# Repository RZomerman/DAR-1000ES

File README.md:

# Sony DAR-1000ES Conversion Project

This repository contains the project documentation converted from the original Word document into chapter-based GitHub Flavored Markdown.

## Chapters

For current AHCT wiring, brightness calculations and radio operation, start
with the [screen-driver operating guide](13-screen-driver-operating-guide.md).
Shared STB on **both** TD chips corrected the earlier multiplexing corruption;
clean 22-matrix text and scrolling were observed. Firmware 0.3.28 includes
internet radio, explicitly authorized full-width NOW PLAYING, and source
channel/bitrate/playback/genre indicators.
Installed 0.3.29 adds selectable Option 1 stereo spectrum (11 real PCM frequency
bands per channel), verified with isolated TD-model captures and decoded
stereo/mono/silence fixtures; the user confirmed the bars at 0.75% brightness.
Version 0.3.30 adds MONO 1/2 bank labels while retaining actual-source STEREO
and fixes measured scan gaps with longer DMA batching. A connected camera
snapshot confirms all 22 bars and STEREO/MONO 1/MONO 2/TUNED at 0.75%
per-grid duty. User confirmation of residual flicker is still pending;
a still image cannot establish temporal stability.
Physical voltage/current validation remains outstanding.
Firmware 0.3.31 boots with the fixed AHCT v2 GPIO map. Display output still
starts stopped; the legacy profile remains an isolated-only runtime option.
Installed firmware 0.3.32 adds eight display modes and shared short-/long-press
controls for a future Display Mode button, with 0.25% / 0.5% / 0.75% DIM cycling.
All eight modes and DIM cycling were checked on the isolated ESP; after
reconnection, Equalizer was restored at 0.75% per-grid duty.

For current display control, start with the
[fixed-element guide](08-esp-display-driver-specification.md#6-fixed-element-control-guide)
and [generic 5x7 matrix guide](08-esp-display-driver-specification.md#7-generic-5x7-matrix-guide).
The [annotated reference comparison](media/display-reference-coverage.svg)
matches every functional symbol in the FL701 drawing to an observed command.
Element mapping is complete at that level. Clean full-screen multiplexing
has now been observed with shared STB; electrical validation remains outstanding.

The [complete display bitmap catalogue](10-display-bitmap-catalogue.md)
includes 5x7 pixel patterns and HEX values for uppercase/lowercase letters,
digits, punctuation, a music note and seven level bars.

1. [DAR-1000ES Conversion](01-conversion.md)
2. [DAR-1000ES Display Control](02-display-control.md)
3. [DAR-1000ES Sound Path](03-sound-path.md)
4. [DAR-1000ES Program and Keypad Baseline](04-program-and-keypad-baseline.md)
5. [Bus Capture Findings and Key Reports](05-bus-capture-findings.md)
6. [Direct Display driving](06-direct-display-driving.md)
7. [Audio Control Findings and Next-Step Plan](07-audio-control-findings-and-plan.md)
8. [ESP32 Display-Driver Specification](08-esp-display-driver-specification.md)
9. [Music Note Bitmap](09-music-note-bitmap.md)
10. [Display Bitmap Catalogue](10-display-bitmap-catalogue.md)
11. [Live ESP32 Display Driver and Validation](11-live-display-driver-and-validation.md)
12. [TD62C950RF Timing Revalidation](12-td62c950rf-timing-revalidation.md)
13. [Screen Driver Operating Guide](13-screen-driver-operating-guide.md)

Images used by the chapters are stored in [`media/`](media/).

The [ESP32 firmware](firmware/README-DAR-1000ES.md) includes internet radio,
the opt-in display timing/NOW PLAYING profile and the preserved upstream license.

## Control Integration Options

1. **Reuse the original controls (partially characterized):** Investigate the parallel bus between the system controller and display/front-panel controller IC701 before bypassing the original control firmware. See the [internal bus protocol specification](SONY_DAR1000ES_Protocol_Spec.md) and [2026-11-02 capture findings](05-bus-capture-findings.md). Passive captures establish repeatable framing and key/display correlations, but masked bits, driver ownership and electrical assumptions still block reliable emulation.
2. **Direct display-driver control (optically mapped, driver experimental):** Captures at IC702/IC703 establish a 26-slot scan, 40 segment clocks and one grid clock per slot. Controlled one-hot tests now map all 770 matrix dots and all fixed functional elements shown in the reference. See the [operating guide](13-screen-driver-operating-guide.md), [element guide](08-esp-display-driver-specification.md) and [capture/validation history](06-direct-display-driving.md). Shared STB on both TD chips now gives clean full-width text and scrolling; electrical margins and current remain unverified. [DAR-1000ES Display Control](02-display-control.md) retains the original hardware proposal, not current wiring instructions.

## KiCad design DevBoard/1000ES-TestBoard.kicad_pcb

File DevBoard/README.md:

# Sony DAR-1000ES ESP32 Development Board

## Overview

**Design proposal, not a hardware-validation report.** This document describes
the intended three-ESP development board, not the pinout of the current
display-test harness. The [current display-control guide](../08-esp-display-driver-specification.md)
records confirmed element mapping; it does not establish that this board's
audio, bus, keypad, power or isolation features have been validated.

This development board is designed as the primary hardware platform for the **Sony DAR-1000ES modernization project**. It enables rapid experimentation with multiple integration strategies while preserving the original Sony hardware wherever possible.

The board incorporates **three ESP32-S3 controllers**, although only two are expected to be required for the final solution. The third controller is included specifically as a contingency path for direct display control if communication through the original Sony system controller (IC701) proves impractical.

The objective of this board is to validate all critical hardware interfaces before committing to a final production design.

---

## Design Goals

The board supports testing of four major functional areas:

### 1. Digital Audio Injection

A dedicated Audio ESP is responsible for generating digital audio and feeding it directly into the Sony audio processing chain.

Target interface:

| Signal | Destination |
|----------|----------|
| ATT/SHIFT/LATCH | IC501 |
| LRCKI | IC501 |
| DATAI | IC501 |
| BCKI | IC501 |

This allows the DAR-1000ES to receive modern digital audio streams while continuing to use the original Sony DAC and audio circuitry.

---

### 2. IC701 Controller Bus Injection

The primary Controller ESP is intended to test emulation and injection on the internal Sony communication bus. **This has not been validated.** This is **Option 1**: investigate retaining IC701, the display/front-panel controller, and the default controls before directly driving IC702 and IC703.

See the [unvalidated internal bus protocol proposal](../SONY_DAR1000ES_Protocol_Spec.md) for the working hypotheses and required validation. Signal directions, timing, electrical assumptions, and message formats are not established.

Supported signals:

| Signal |
|----------|
| DBS0-DBS7 |
| ACK |
| STB |
| REQ |
| NCK |

The intention is to determine whether the original firmware architecture can be leveraged by communicating with IC701 over its interface to the system controller.

If successful, this becomes the preferred approach because it preserves most of the original Sony subsystem interactions.

---

### 2b. Direct Sony Hardware Control

In addition to bus injection, the Controller ESP can directly control critical DAR-1000ES hardware signals.

Supported outputs include:

| Function |
|----------|
| D.MUTE |
| A.MUTE |
| Audio Relay |
| Power Control |
| Reset Control |

These are intended control outputs, not established safe drive procedures.
Verify their actual voltage, polarity, ownership and reset behavior before
using them, even if communication through the original controller fails.

---

### 2c. Keypad Matrix Interface

The board provides direct access to the original Sony button matrix.

Capabilities:

- Scan front-panel buttons
- Decode keypad presses
- Replace original controller functionality
- Support future custom user interface options

The proposed keypad interface uses a dedicated keypad controller. Isolate
IC701 from all fourteen matrix nets before enabling another scanner;
reliable operation and physical key positions still need validation.
See the [keypad design baseline](../04-program-and-keypad-baseline.md).

---

### 3. Direct Display Driver Control (Fallback Strategy)

A third ESP32-S3 is included exclusively as a backup solution.

If direct IC701 bus injection does not provide sufficient control of the front-panel display, this ESP can take over the display subsystem directly.

Target functionality includes:

- Direct control of display driver ICs
- Row driving
- Column driving
- Segment updates
- Custom display rendering

This completely bypasses the original display control architecture and provides maximum flexibility for future software development.

---

## Controller Architecture

### Audio ESP

Primary responsibility:

- Streaming audio reception
- Audio decoding
- I²S generation
- Interface to IC501

Interfaces:

- Audio output signals
- UART communication with Controller ESP

---

### Controller ESP

Primary responsibility:

- System orchestration
- IC701 bus injection
- Sony hardware control
- Keypad processing

Interfaces:

- Bus emulation
- Control outputs
- Keypad matrix
- UART communication

---

### Display ESP

Primary responsibility:

- Display subsystem experimentation
- Direct display driver control
- Fallback display architecture

Interfaces:

- Row control
- Column control
- UART communication

---

## ESP-to-ESP Communication

The three ESP32 controllers can communicate through dedicated UART links.

This architecture allows:

- Separation of audio processing from system control
- Reduced software complexity
- Independent firmware development
- Easier debugging and validation

The Audio ESP and Display ESP act as peripherals while the Controller ESP functions as the primary coordinator.

---

## Power Architecture

Although each ESP controller has its own USB-C connector, USB is intended primarily for:

- Firmware upload
- Debugging
- Serial console access

Normal operating power is supplied directly from the Sony DAR-1000ES.

Features include:

- Independent ESP enable/disable jumpers
- Selective controller isolation
- Simplified troubleshooting
- Reduced power consumption during testing

This allows any controller to be disabled while maintaining operation of the remaining subsystems.

Disabling a controller or its power jumper does not by itself establish
electrical isolation of its signal pins. Verify buffer enables, power-state
behavior and original-controller ownership; do not assume an unpowered ESP
or Sony input is safe to back-drive.

---

## PCB Design Philosophy

To minimize manufacturing cost and simplify assembly, the PCB has been intentionally designed as a:

**Single-layer board**

Characteristics:

- Single copper layer
- Limited number of wire bridges
- Large ground areas
- Easy inspection and rework
- Low fabrication cost

The use of a mostly single-sided layout also makes future modifications straightforward during the experimental phase of the project.

---

## Development Strategy

The board is intended to validate three possible integration levels:

### Level 1 – Audio Only

- Audio ESP operational
- Original Sony control system retained

### Level 2 – IC701 Emulation

- Controller ESP injects Sony bus traffic
- Original display drivers retained
- Original Sony architecture largely preserved

### Level 3 – Full Replacement

- Controller ESP replaces IC701 functionality
- Display ESP directly drives display hardware
- Complete modern control stack running on ESP32 controllers

---

## Current Status

This development-board design is a proposed validation platform for the
DAR-1000ES retrofit effort, not proof of a tested complete hardware platform.

The modular three-ESP architecture provides multiple fallback paths, ensuring that all major subsystems can be independently evaluated before a final production design is selected.

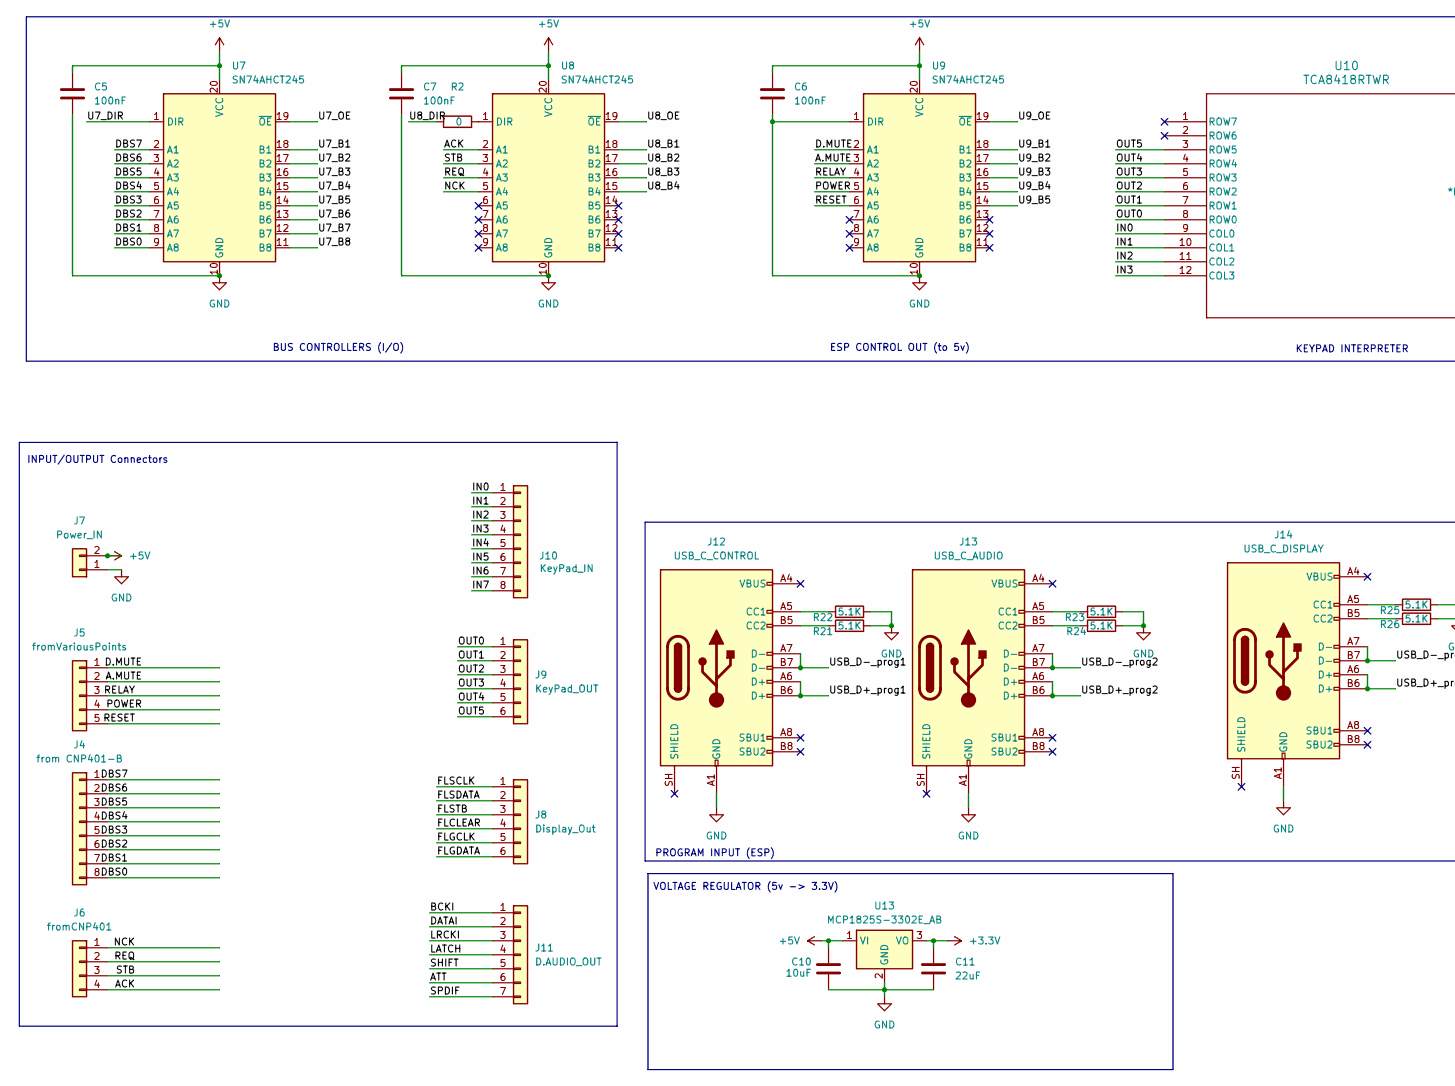
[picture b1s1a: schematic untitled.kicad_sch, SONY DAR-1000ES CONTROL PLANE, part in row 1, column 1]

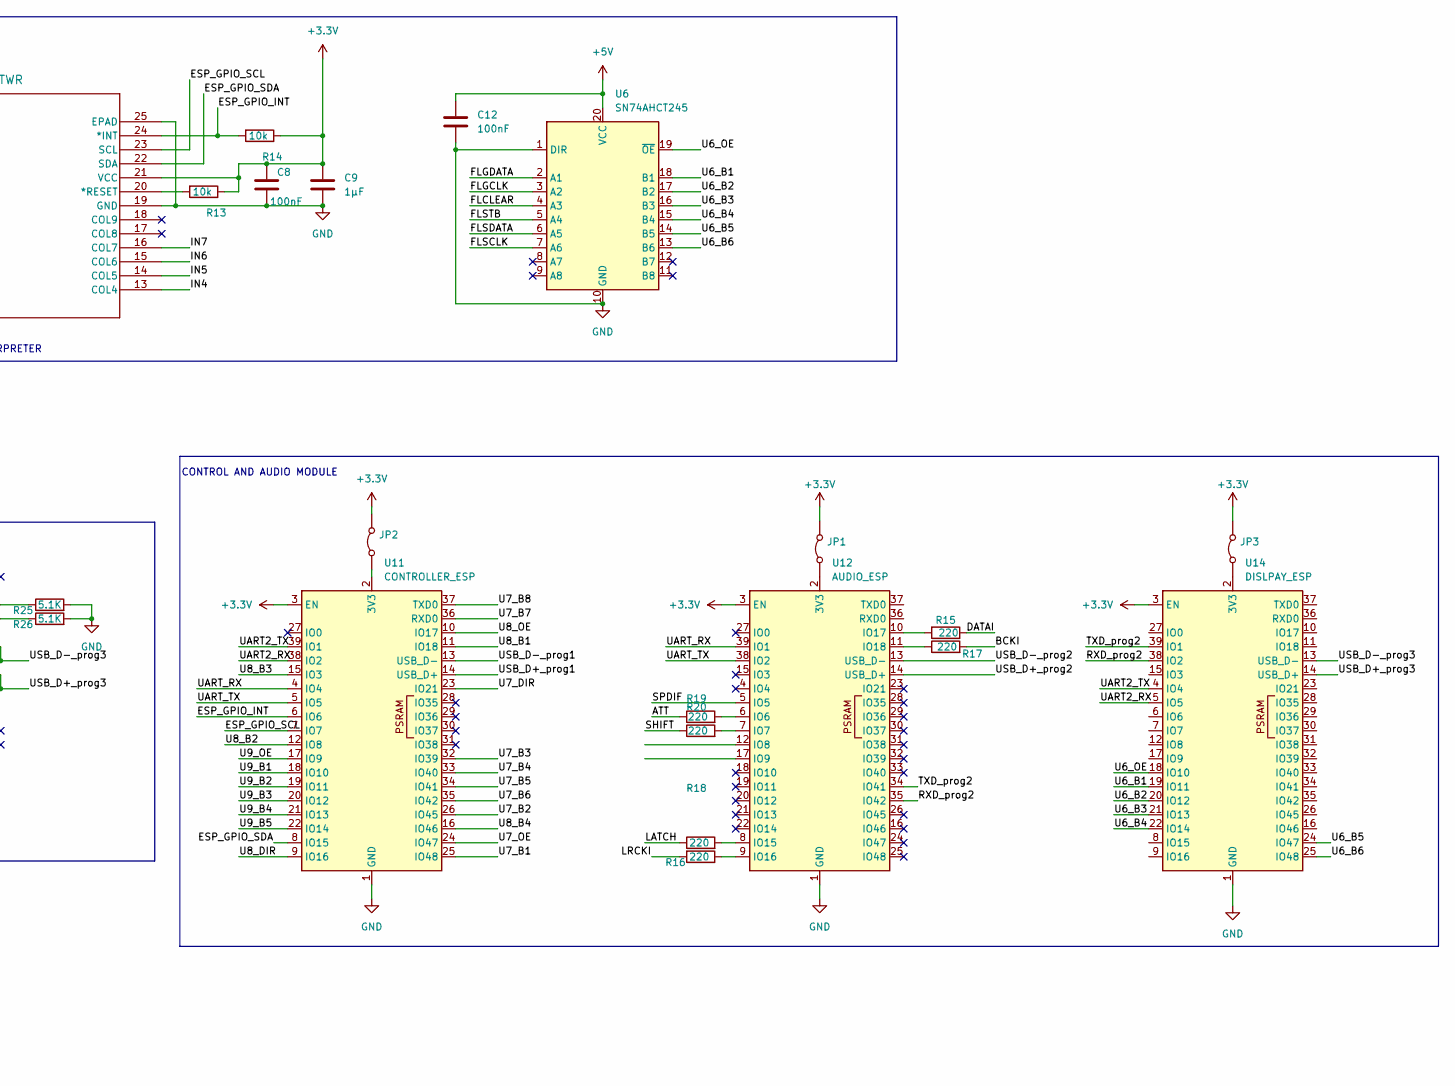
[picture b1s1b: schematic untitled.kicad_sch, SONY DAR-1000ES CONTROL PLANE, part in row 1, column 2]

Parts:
C5, C6, C7, C8, C12: 100nF; C_Elec_4x5.4
C9: 1µF; C_Elec_4x5.4
C10: 10uF; C_Elec_4x5.4
C11: 22uF; C_Elec_4x5.4
J4: from CNP401-B; JST_PH_B8B-PH-K_1x08_P2.00mm_Vertical
J5: fromVariousPoints; JST_PH_B5B-PH-K_1x05_P2.00mm_Vertical
J6: fromCNP401; JST_PH_B4B-PH-K_1x04_P2.00mm_Vertical
J7: Power_IN; JST_PH_B2B-PH-K_1x02_P2.00mm_Vertical
J8: Display_Out; JST_PH_B8B-PH-K_1x08_P2.00mm_Vertical
J9: KeyPad_OUT; JST_PH_B6B-PH-K_1x06_P2.00mm_Vertical
J10: KeyPad_IN; JST_PH_B8B-PH-K_1x08_P2.00mm_Vertical
J11: D.AUDIO_OUT; JST_PH_B7B-PH-K_1x07_P2.00mm_Vertical
J12: USB_C_CONTROL; USB_C_Receptacle_GCT_USB4105-xx-A_16P_TopMnt_Horizontal
J13: USB_C_AUDIO; USB_C_Receptacle_GCT_USB4105-xx-A_16P_TopMnt_Horizontal
J14: USB_C_DISPLAY; USB_C_Receptacle_GCT_USB4105-xx-A_16P_TopMnt_Horizontal
JP1, JP2, JP3: Jumper_2_Bridged; SolderJumper-2_P1.3mm_Bridged2Bar_Pad1.0x1.5mm
R2: 0; R_Axial_DIN0204_L3.6mm_D1.6mm_P5.08mm_Horizontal
R13, R14: 10k; R_0508_1220Metric_Pad1.12x2.15mm_HandSolder
R15, R16, R17, R18, R19, R20: 220; R_0508_1220Metric_Pad1.12x2.15mm_HandSolder
R21, R22, R23, R24, R25, R26: 5.1K; R_0508_1220Metric_Pad1.12x2.15mm_HandSolder
U6, U7, U8, U9: SN74AHCT245; TSSOP-20_4.4x6.5mm_P0.65mm
U10: TCA8418RTWR; QFN-24-1EP_4x4mm_P0.5mm_EP2.7x2.7mm
U11: CONTROLLER_ESP; ESP32-S3-WROOM-1
U12: AUDIO_ESP; ESP32-S3-WROOM-1
U13: MCP1825S-3302E_AB; TO-220-3_Vertical
U14: DISLPAY_ESP; ESP32-S3-WROOM-1

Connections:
+3.3V: C8.1, C9.1, C11.1, JP1.2 (B), JP2.2 (B), JP3.2 (B), R13.1, R14.1, U10.21 (VCC), U11.3 (EN), U12.3 (EN), U13.3 (VO), U14.3 (EN); also elsewhere on the board
+5V: C5.1, C6.1, C7.1, C10.1, C12.1, J7.2, U6.20 (VCC), U7.20 (VCC), U8.20 (VCC), U9.20 (VCC), U13.1 (VI)
/ES1000-Default/A.MUTE: J5.2, U9.3 (A2)
/ES1000-Default/ACK: J6.4, U8.2 (A1)
/ES1000-Default/ATT: J11.6, R20.1
/ES1000-Default/BCKI: J11.1, R17.2
/ES1000-Default/D.MUTE: J5.1, U9.2 (A1)
/ES1000-Default/DATAI: J11.2, R15.1
/ES1000-Default/DBS0: J4.8, U7.9 (A8)
/ES1000-Default/DBS1: J4.7, U7.8 (A7)
/ES1000-Default/DBS2: J4.6, U7.7 (A6)
/ES1000-Default/DBS3: J4.5, U7.6 (A5)
/ES1000-Default/DBS4: J4.4, U7.5 (A4)
/ES1000-Default/DBS5: J4.3, U7.4 (A3)
/ES1000-Default/DBS6: J4.2, U7.3 (A2)
/ES1000-Default/DBS7: J4.1, U7.2 (A1)
/ES1000-Default/ESP_GPIO_INT: R14.2, U10.24 (*INT), U11.6 (IO6)
/ES1000-Default/ESP_GPIO_SCL: U10.23 (SCL), U11.7 (IO7)
/ES1000-Default/ESP_GPIO_SDA: U10.22 (SDA), U11.8 (IO15)
/ES1000-Default/FLCLEAR: J8.4, U6.4 (A3)
/ES1000-Default/FLGCLK: J8.5, U6.3 (A2)
/ES1000-Default/FLGDATA: J8.6, U6.2 (A1)
/ES1000-Default/FLSCLK: J8.1, U6.7 (A6)
/ES1000-Default/FLSDATA: J8.2, U6.6 (A5)
/ES1000-Default/FLSTB: J8.3, U6.5 (A4)
/ES1000-Default/IN0: J10.1, U10.9 (COL0)
/ES1000-Default/IN1: J10.2, U10.10 (COL1)
/ES1000-Default/IN2: J10.3, U10.11 (COL2)
/ES1000-Default/IN3: J10.4, U10.12 (COL3)
/ES1000-Default/IN4: J10.5, U10.13 (COL4)
/ES1000-Default/IN5: J10.6, U10.14 (COL5)
/ES1000-Default/IN6: J10.7, U10.15 (COL6)
/ES1000-Default/IN7: J10.8, U10.16 (COL7)
/ES1000-Default/LATCH: J11.4, R18.1
/ES1000-Default/LRCKI: J11.3, R16.2
/ES1000-Default/NCK: J6.1, U8.5 (A4)
/ES1000-Default/OUT0: J9.1, U10.8 (ROW0)
/ES1000-Default/OUT1: J9.2, U10.7 (ROW1)
/ES1000-Default/OUT2: J9.3, U10.6 (ROW2)
/ES1000-Default/OUT3: J9.4, U10.5 (ROW3)
/ES1000-Default/OUT4: J9.5, U10.4 (ROW4)
/ES1000-Default/OUT5: J9.6, U10.3 (ROW5)
/ES1000-Default/POWER: J5.4, U9.5 (A4)
/ES1000-Default/RELAY: J5.3, U9.4 (A3)
/ES1000-Default/REQ: J6.2, U8.4 (A3)
/ES1000-Default/RESET: J5.5, U9.6 (A5)
/ES1000-Default/RXD_prog2: U12.35 (IO42), U14.38 (IO2)
/ES1000-Default/SHIFT: J11.5, R19.1
/ES1000-Default/SPDIF: J11.7, U12.5 (IO5)
/ES1000-Default/STB: J6.3, U8.3 (A2)
/ES1000-Default/TXD_prog2: U12.34 (IO41), U14.39 (IO1)
/ES1000-Default/U6_B1: U6.18 (B1), U14.19 (IO11)
/ES1000-Default/U6_B2: U6.17 (B2), U14.20 (IO12)
/ES1000-Default/U6_B3: U6.16 (B3), U14.21 (IO13)
/ES1000-Default/U6_B4: U6.15 (B4), U14.22 (IO14)
/ES1000-Default/U6_B5: U6.14 (B5), U14.24 (IO47)
/ES1000-Default/U6_B6: U6.13 (B6), U14.25 (IO48)
/ES1000-Default/U6_OE: U6.19 (~OE), U14.18 (IO10)
/ES1000-Default/U7_B1: U7.18 (B1), U11.25 (IO48)
/ES1000-Default/U7_B2: U7.17 (B2), U11.26 (IO45)
/ES1000-Default/U7_B3: U7.16 (B3), U11.32 (IO39)
/ES1000-Default/U7_B4: U7.15 (B4), U11.33 (IO40)
/ES1000-Default/U7_B5: U7.14 (B5), U11.34 (IO41)
/ES1000-Default/U7_B6: U7.13 (B6), U11.35 (IO42)
/ES1000-Default/U7_B7: U7.12 (B7), U11.36 (RXD0)
/ES1000-Default/U7_B8: U7.11 (B8), U11.37 (TXD0)
/ES1000-Default/U7_DIR: U7.1 (DIR), U11.23 (IO21)
/ES1000-Default/U7_OE: U7.19 (~OE), U11.24 (IO47)
/ES1000-Default/U8_B1: U8.18 (B1), U11.11 (IO18)
/ES1000-Default/U8_B2: U8.17 (B2), U11.12 (IO8)
/ES1000-Default/U8_B3: U8.16 (B3), U11.15 (IO3)
/ES1000-Default/U8_B4: U8.15 (B4), U11.16 (IO46)
/ES1000-Default/U8_DIR: R2.1, U11.9 (IO16)
/ES1000-Default/U8_OE: U8.19 (~OE), U11.10 (IO17)
/ES1000-Default/U9_B1: U9.18 (B1), U11.18 (IO10)
/ES1000-Default/U9_B2: U9.17 (B2), U11.19 (IO11)
/ES1000-Default/U9_B3: U9.16 (B3), U11.20 (IO12)
/ES1000-Default/U9_B4: U9.15 (B4), U11.21 (IO13)
/ES1000-Default/U9_B5: U9.14 (B5), U11.22 (IO14)
/ES1000-Default/U9_OE: U9.19 (~OE), U11.17 (IO9)
/ES1000-Default/UART2_RX: U11.38 (IO2), U14.5 (IO5)
/ES1000-Default/UART2_TX: U11.39 (IO1), U14.4 (IO4)
/ES1000-Default/UART_RX: U11.4 (IO4), U12.39 (IO1)
/ES1000-Default/UART_TX: U11.5 (IO5), U12.38 (IO2)
/ES1000-Default/USB_D+_prog1: J12.A6 (D+), J12.B6 (D+), U11.14 (USB_D+)
/ES1000-Default/USB_D+_prog2: J13.A6 (D+), J13.B6 (D+), U12.14 (USB_D+)
/ES1000-Default/USB_D+_prog3: J14.A6 (D+), J14.B6 (D+), U14.14 (USB_D+)
/ES1000-Default/USB_D-_prog1: J12.A7 (D-), J12.B7 (D-), U11.13 (USB_D-)
/ES1000-Default/USB_D-_prog2: J13.A7 (D-), J13.B7 (D-), U12.13 (USB_D-)
/ES1000-Default/USB_D-_prog3: J14.A7 (D-), J14.B7 (D-), U14.13 (USB_D-)
GND: C5.2, C6.2, C7.2, C8.2, C9.2, C10.2, C11.2, C12.2, J7.1, J8.8, J12.A1 (GND), J12.A12 (GND), J12.B1 (GND), J12.B12 (GND), J13.A1 (GND), J13.A12 (GND), J13.B1 (GND), J13.B12 (GND), J14.A1 (GND), J14.A12 (GND), J14.B1 (GND), J14.B12 (GND), R21.2, R22.2, R23.2, R24.2, R25.2, R26.2, U6.1 (DIR), U6.10 (GND), U7.10 (GND), U8.10 (GND), U9.1 (DIR), U9.10 (GND), U10.19 (GND), U10.25 (EPAD), U11.1 (GND), U11.40 (GND), U11.41 (GND), U12.1 (GND), U12.40 (GND), U12.41 (GND), U13.2 (GND), U14.1 (GND), U14.40 (GND), U14.41 (GND)
unnamed: J12.A5 (CC1), R22.1
unnamed: J12.B5 (CC2), R21.1
unnamed: J13.A5 (CC1), R23.1
unnamed: J13.B5 (CC2), R24.1
unnamed: J14.A5 (CC1), R25.1
unnamed: J14.B5 (CC2), R26.1
unnamed: JP1.1 (A), U12.2 (3V3)
unnamed: JP2.1 (A), U11.2 (3V3)
unnamed: JP3.1 (A), U14.2 (3V3)
unnamed: R2.2, U8.1 (DIR)
unnamed: R13.2, U10.20 (*RESET)
unnamed: R20.2, U12.6 (IO6)
unnamed: R19.2, U12.7 (IO7)
unnamed: R18.2, U12.8 (IO15)
unnamed: R16.1, U12.9 (IO16)
unnamed: R15.2, U12.10 (IO17)
unnamed: R17.1, U12.11 (IO18)

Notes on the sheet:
BUS CONTROLLERS (I/O)
VOLTAGE REGULATOR (5v -> 3.3V)
ESP CONTROL OUT (to 5v)
KEYPAD INTERPRETER
INPUT/OUTPUT Connectors
PROGRAM INPUT (ESP)
CONTROL AND AUDIO MODULE

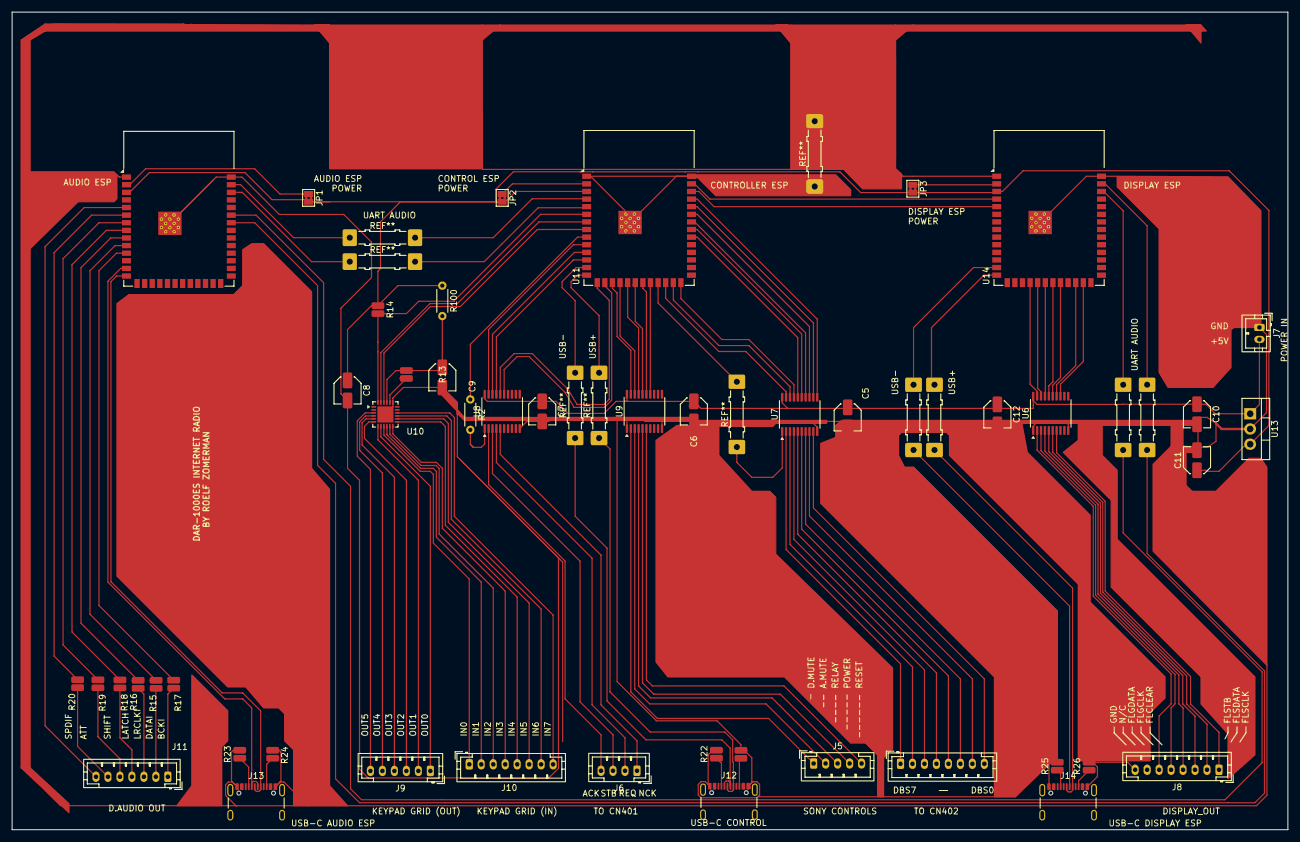
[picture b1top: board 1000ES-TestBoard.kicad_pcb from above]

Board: 2 copper layers, 213.0 x 136.5 mm, 47 parts (0 on the bottom side), 108 nets.

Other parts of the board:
R100: 0; R_Axial_DIN0204_L3.6mm_D1.6mm_P5.08mm_Horizontal

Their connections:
+3.3V: R100.1, R100.2; also elsewhere on the board

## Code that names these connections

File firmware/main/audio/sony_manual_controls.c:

#include "sony_manual_controls.h"

#include "driver/gpio.h"
#include "esp_log.h"
#include "esp_rom_sys.h"
#include "esp_timer.h"
#include "freertos/FreeRTOS.h"
#include "freertos/semphr.h"
#include "freertos/task.h"
#include <string.h>

typedef struct {
  const char *name;
  gpio_num_t gpio;
  int level;
} control_t;

static control_t controls[] = {
    {"d_mute", GPIO_NUM_10, 0},
    {"a_mute", GPIO_NUM_11, 0},
    {"relay", GPIO_NUM_12, -1},
    {"init", GPIO_NUM_2, -1},
    {"att", GPIO_NUM_4, -1},
    {"shift", GPIO_NUM_5, -1},
    {"latch", GPIO_NUM_6, -1},
};
enum { D_MUTE, A_MUTE, RELAY, INIT, ATT, SHIFT, LATCH };
static const char *TAG = "sony_controls";
static SemaphoreHandle_t control_lock;

esp_err_t sony_manual_controls_init(void) {
  control_lock = xSemaphoreCreateMutex();
  if (!control_lock) return ESP_ERR_NO_MEM;

  gpio_config_t input = {
      .pin_bit_mask = (1ULL << GPIO_NUM_10) | (1ULL << GPIO_NUM_11) |
                      (1ULL << GPIO_NUM_12) | (1ULL << GPIO_NUM_2) |
                      (1ULL << GPIO_NUM_4) | (1ULL << GPIO_NUM_5) |
                      (1ULL << GPIO_NUM_6),
      .mode = GPIO_MODE_INPUT,
      .pull_up_en = GPIO_PULLUP_DISABLE,
      .pull_down_en = GPIO_PULLDOWN_DISABLE,
      .intr_type = GPIO_INTR_DISABLE,
  };
  esp_err_t err = gpio_config(&input);
  if (err != ESP_OK) return err;
  for (size_t i = 0; i < 2; ++i) {
    err = gpio_set_level(controls[i].gpio, 0);
    if (err != ESP_OK) return err;
    err = gpio_set_direction(controls[i].gpio, GPIO_MODE_INPUT_OUTPUT);
    if (err != ESP_OK) return err;
  }
  return ESP_OK;
}

static esp_err_t set_pin(control_t *pin, int level) {
  esp_err_t err = gpio_set_level(pin->gpio, (uint32_t)level);
  if (err == ESP_OK && pin->level < 0)
    err = gpio_set_direction(pin->gpio, GPIO_MODE_INPUT_OUTPUT);
  if (err == ESP_OK) pin->level = level;
  return err;
}

esp_err_t sony_manual_controls_set(const char *signal, int level) {
  if (!signal || (level != 0 && level != 1)) return ESP_ERR_INVALID_ARG;
  control_t *pin = NULL;
  for (size_t i = 0; i < sizeof(controls) / sizeof(controls[0]); ++i)
    if (strcmp(signal, controls[i].name) == 0) pin = &controls[i];
  if (!pin) return ESP_ERR_INVALID_ARG;
  if (!control_lock) return ESP_ERR_INVALID_STATE;
  if (xSemaphoreTake(control_lock, portMAX_DELAY) != pdTRUE) return ESP_ERR_TIMEOUT;
  esp_err_t err = set_pin(pin, level);
  xSemaphoreGive(control_lock);
  return err;
}

static void wait_until(int64_t deadline) {
  int64_t remaining;
  while ((remaining = deadline - esp_timer_get_time()) > 0) {
    if (remaining > 2000) vTaskDelay(1);
    else esp_rom_delay_us((uint32_t)remaining);
  }
}

static esp_err_t shift_bits(const char *bits, unsigned high_us, unsigned low_us) {
  for (size_t i = 0; bits[i]; ++i) {
    esp_err_t err = set_pin(&controls[ATT], bits[i] == '1');
    if (err != ESP_OK) return err;
    esp_rom_delay_us(1);
    err = set_pin(&controls[SHIFT], 1);
    if (err != ESP_OK) return err;
    esp_rom_delay_us(high_us);
    err = set_pin(&controls[SHIFT], 0);
    if (err != ESP_OK) return err;
    esp_rom_delay_us(low_us);
  }
  return ESP_OK;
}

static esp_err_t latched_word(const char *bits) {
  esp_err_t err = set_pin(&controls[LATCH], 1);
  if (err != ESP_OK) return err;
  esp_rom_delay_us(10);
  err = shift_bits(bits, 2, 1);
  if (err != ESP_OK) return err;
  esp_rom_delay_us(7);
  return set_pin(&controls[LATCH], 0);
}

esp_err_t sony_manual_controls_replay_startup(void) {
  static const char burst[] =
      "001000101011000000000000000010000000000000000000"
      "000000011001101101000000000001111011011011110000";
  static const char first[] = "0011010000100010";
  static const char second[] = "0000000000100000";
  static const char initial_24[] = "001000101011000000000000";
  if (!control_lock) return ESP_ERR_INVALID_STATE;
  if (xSemaphoreTake(control_lock, portMAX_DELAY) != pdTRUE) return ESP_ERR_TIMEOUT;
  if (controls[INIT].level != 1 || controls[D_MUTE].level != 0 ||
      controls[A_MUTE].level != 0) {
    xSemaphoreGive(control_lock);
    return ESP_ERR_INVALID_STATE;
  }
  esp_err_t err = set_pin(&controls[LATCH], 0);
  if (err == ESP_OK) err = set_pin(&controls[SHIFT], 0);
  if (err == ESP_OK) err = set_pin(&controls[ATT], 0);
  int64_t start = esp_timer_get_time();
  if (err == ESP_OK) {
    wait_until(start + 57229);
    err = set_pin(&controls[LATCH], 1);
  }
  if (err == ESP_OK) {
    wait_until(start + 125413);
    err = set_pin(&controls[LATCH], 0);
  }
  if (err == ESP_OK) {
    wait_until(start + 159692);
    err = shift_bits(burst, 4, 3);
  }
  if (err == ESP_OK) {
    wait_until(start + 808830);
    err = latched_word(first);
  }
  if (err == ESP_OK) {
    esp_rom_delay_us(32);
    err = latched_word(second);
  }
  if (err == ESP_OK) {
    wait_until(start + 856650);
    err = shift_bits(initial_24, 4, 3);
  }
  for (size_t i = ATT; i <= LATCH; ++i) {
    esp_err_t cleanup = set_pin(&controls[i], 0);
    if (cleanup != ESP_OK) {
      ESP_LOGE(TAG, "Cannot set %s LOW: %s", controls[i].name,
               esp_err_to_name(cleanup));
      if (err == ESP_OK) err = cleanup;
    }
  }
  xSemaphoreGive(control_lock);
  return err;
}

esp_err_t sony_manual_controls_status(cJSON *root) {
  if (!control_lock) return ESP_ERR_INVALID_STATE;
  if (xSemaphoreTake(control_lock, portMAX_DELAY) != pdTRUE) return ESP_ERR_TIMEOUT;
  cJSON *status = cJSON_AddObjectToObject(root, "sony_controls");
  if (!status) {
    xSemaphoreGive(control_lock);
    return ESP_ERR_NO_MEM;
  }
  for (size_t i = 0; i < sizeof(controls) / sizeof(controls[0]); ++i) {
    cJSON *pin = cJSON_AddObjectToObject(status, controls[i].name);
    if (!pin || !cJSON_AddNumberToObject(pin, "gpio", controls[i].gpio) ||
        !(controls[i].level < 0 ? cJSON_AddNullToObject(pin, "level") :
          cJSON_AddNumberToObject(pin, "level", controls[i].level))) {
      xSemaphoreGive(control_lock);
      return ESP_ERR_NO_MEM;
    }
  }
  xSemaphoreGive(control_lock);
  return ESP_OK;
}
